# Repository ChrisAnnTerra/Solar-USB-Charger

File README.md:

## DIY Solar Battery Charger

Power Electronics Class project for ENGR 460. This project was intended for personal use of hobbyist level electronics. 

### Please Refer to the Wiki for further documentation, circuit description, testing notes, and state of the project.

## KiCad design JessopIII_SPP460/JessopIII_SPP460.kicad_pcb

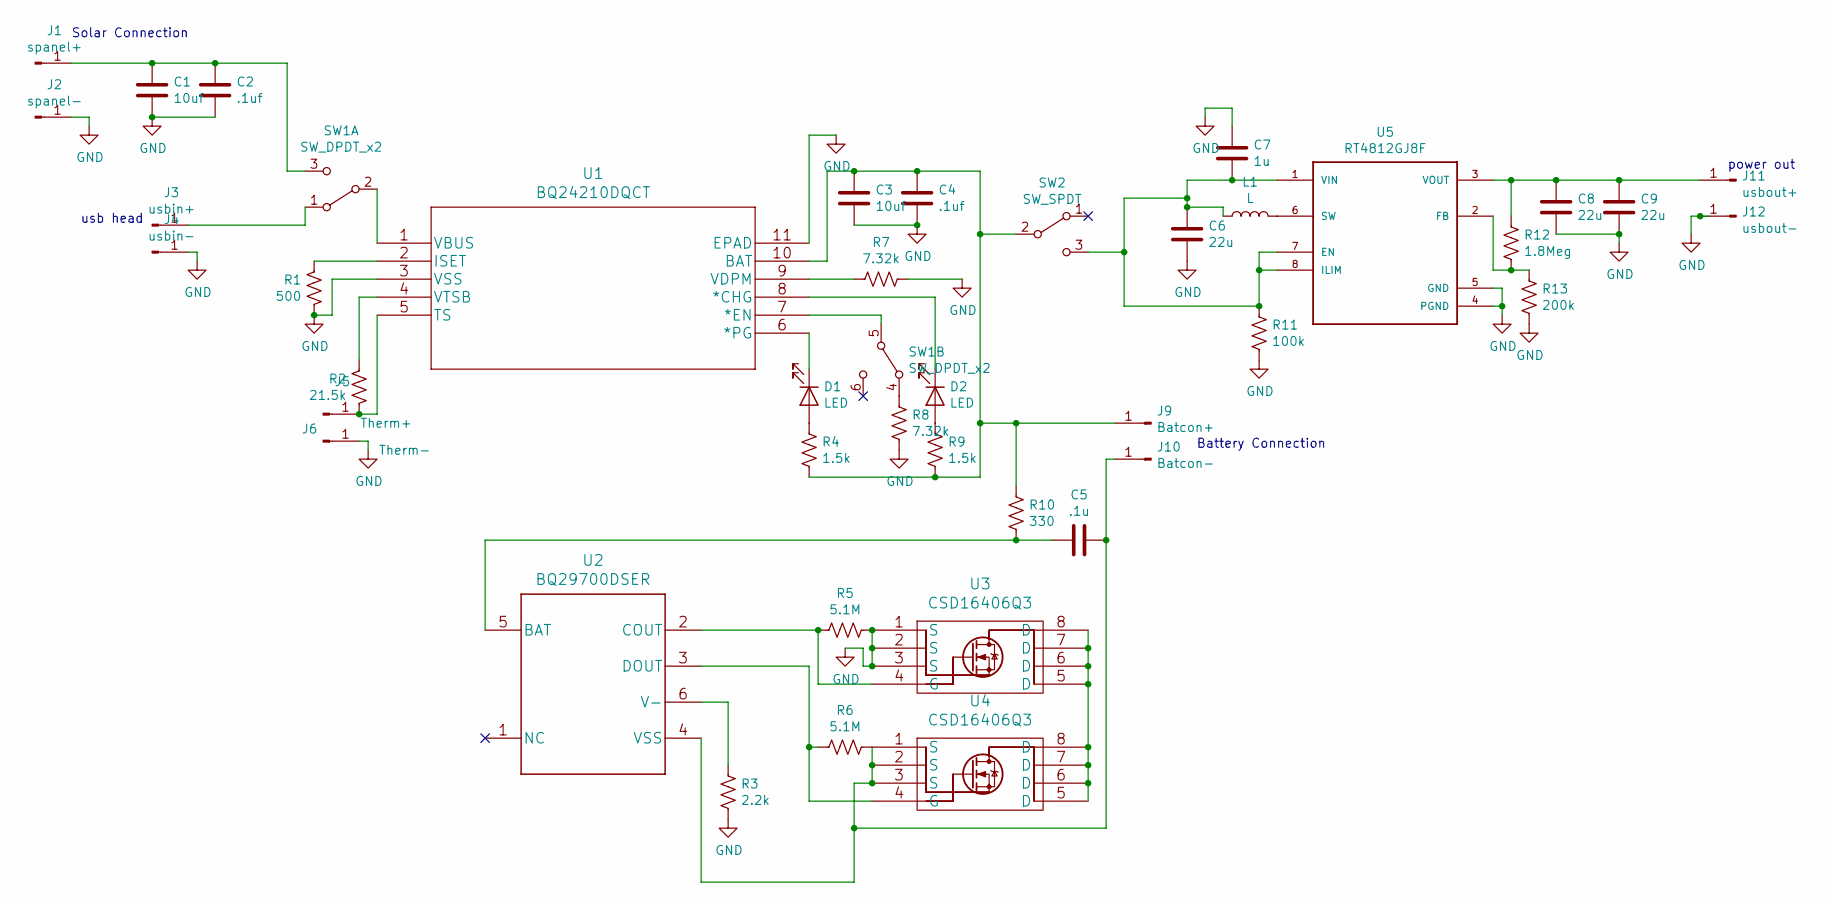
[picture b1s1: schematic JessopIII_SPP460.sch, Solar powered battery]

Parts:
C1, C3: 10uf; C_0805_2012Metric
C2, C4: .1uf; C_0805_2012Metric
C5: .1u; C_0805_2012Metric
C6, C8, C9: 22u; C_0805_2012Metric
C7: 1u; C_0805_2012Metric
D1, D2: LED; LED_0805_2012Metric
J1: spanel+; SolderWirePad_1x01_Drill1mm
J2: spanel-; SolderWirePad_1x01_Drill1mm
J3: usbin+; SolderWirePad_1x01_Drill1mm
J4: usbin-; SolderWirePad_1x01_Drill1mm
J5: Therm+; SolderWirePad_1x01_Drill1mm
J6: Therm-; SolderWirePad_1x01_Drill1mm
J9: Batcon+; SolderWirePad_1x01_Drill1.5mm
J10: Batcon-; SolderWirePad_1x01_Drill1.5mm
J11: usbout+; SolderWirePad_1x01_Drill1mm
J12: usbout-; SolderWirePad_1x01_Drill1mm
L1: L; L_Bourns-SRN6028
R1: 500; R_0805_2012Metric
R2: 21.5k; R_0805_2012Metric
R3: 2.2k; R_0805_2012Metric
R4, R9: 1.5k; R_0805_2012Metric
R5, R6: 5.1M; R_0805_2012Metric
R7, R8: 7.32k; R_0805_2012Metric
R10: 330; R_0805_2012Metric
R11: 100k; R_0805_2012Metric
R12: 1.8Meg; R_0805_2012Metric
R13: 200k; R_0805_2012Metric
SW1: SW_DPDT_x2; SW_CuK_JS202011CQN_DPDT_Straight
SW2: SW_SPDT; PinSocket_1x03_P2.54mm_Vertical
U1: BQ24210DQCT
U2: BQ29700DSER
U3, U4: CSD16406Q3; TRANS_CSD17575Q3
U5: RT4812GJ8F; SOT65P279X100-8N

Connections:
GND: C1.2, C2.2, C3.2, C4.2, C6.2, C7.1, C8.2, C9.2, J2.1, J4.1, J6.1, J12.1, R1.1, R3.2, R5.1, R7.1, R8.2, R11.2, R13.2, U1.3 (VSS), U1.11 (EPAD), U3.1 (S), U3.2 (S), U3.3 (S), U5.4 (PGND), U5.5 (GND)
unnamed: C1.1, C2.1, J1.1, SW1.3 (C)
unnamed: C3.1, C4.1, J9.1, R4.2, R9.2, R10.1, SW2.2 (B), U1.10 (BAT)
unnamed: C5.1, J10.1, R6.1, U2.4 (VSS), U4.1 (S), U4.2 (S), U4.3 (S)
unnamed: C5.2, R10.2, U2.5 (BAT)
unnamed: C6.1, C7.2, L1.1, R11.1, SW2.3 (C), U5.1 (VIN), U5.7 (EN), U5.8 (ILIM)
unnamed: C8.1, C9.1, J11.1, R12.1, U5.3 (VOUT)
unnamed: D1.1 (K), U1.6 (*PG)
unnamed: D1.2 (A), R4.1
unnamed: D2.1 (K), U1.8 (*CHG)
unnamed: D2.2 (A), R9.1
unnamed: J3.1, SW1.1 (A)
unnamed: J5.1, R2.1, U1.5 (TS)
unnamed: L1.2, U5.6 (SW)
unnamed: R1.2, U1.2 (ISET)
unnamed: R2.2, U1.4 (VTSB)
unnamed: R3.1, U2.6 (V-)
unnamed: R5.2, U2.2 (COUT), U3.4 (G)
unnamed: R6.2, U2.3 (DOUT), U4.4 (G)
unnamed: R7.2, U1.9 (VDPM)
unnamed: R8.1, SW1.4 (A)
unnamed: R12.2, R13.1, U5.2 (FB)
unnamed: SW1.2 (B), U1.1 (VBUS)
unnamed: SW1.5 (B), U1.7 (*EN)
unnamed: U3.5 (D), U3.6 (D), U3.7 (D), U3.8 (D), U4.5 (D), U4.6 (D), U4.7 (D), U4.8 (D)

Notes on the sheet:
usb head
Battery Connection
Solar Connection
power out

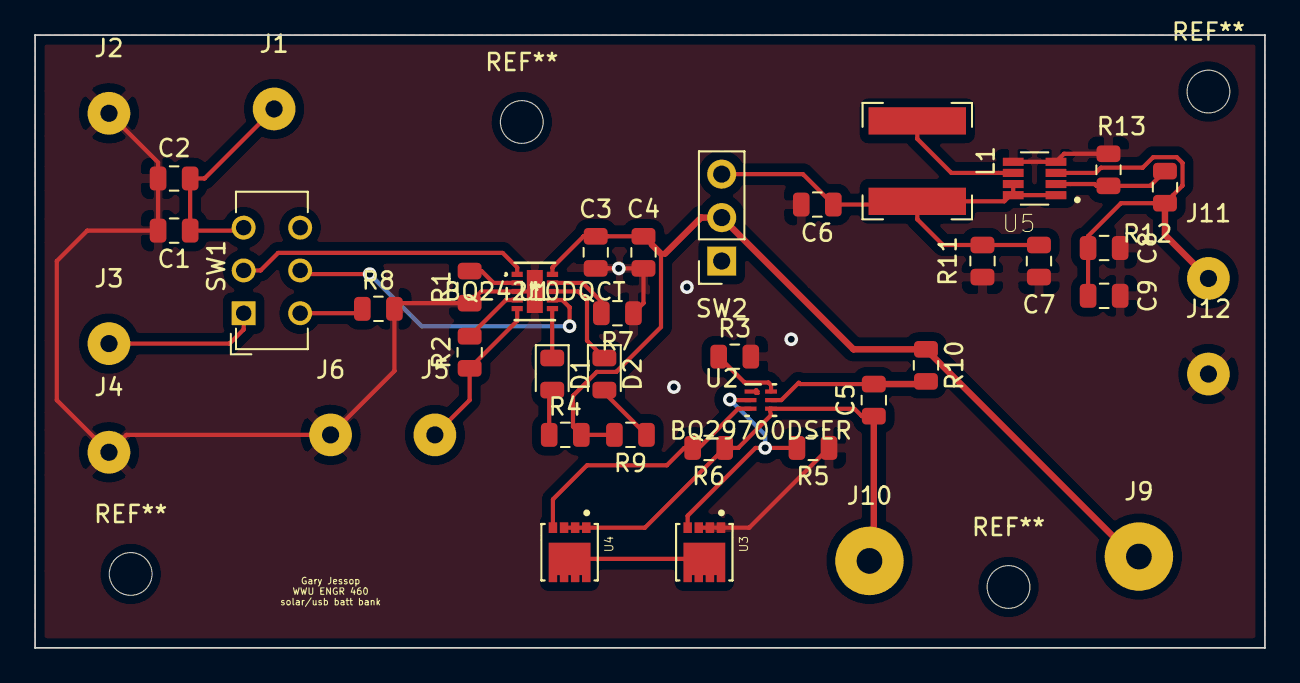
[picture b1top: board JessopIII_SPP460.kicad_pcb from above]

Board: 2 copper layers, 71.9 x 35.8 mm, 42 parts (0 on the bottom side), 25 nets.

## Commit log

2020-06-02 Set theme jekyll-theme-hacker
2020-06-02 Uploading Gary's PCB design

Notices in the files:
parts and their libraries:
Copyright 2016 Accelerated Designs. All rights reserved.
